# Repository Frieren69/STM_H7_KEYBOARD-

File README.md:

# STM_H7_KEYBOARD-
An keyboard with STM 32H7

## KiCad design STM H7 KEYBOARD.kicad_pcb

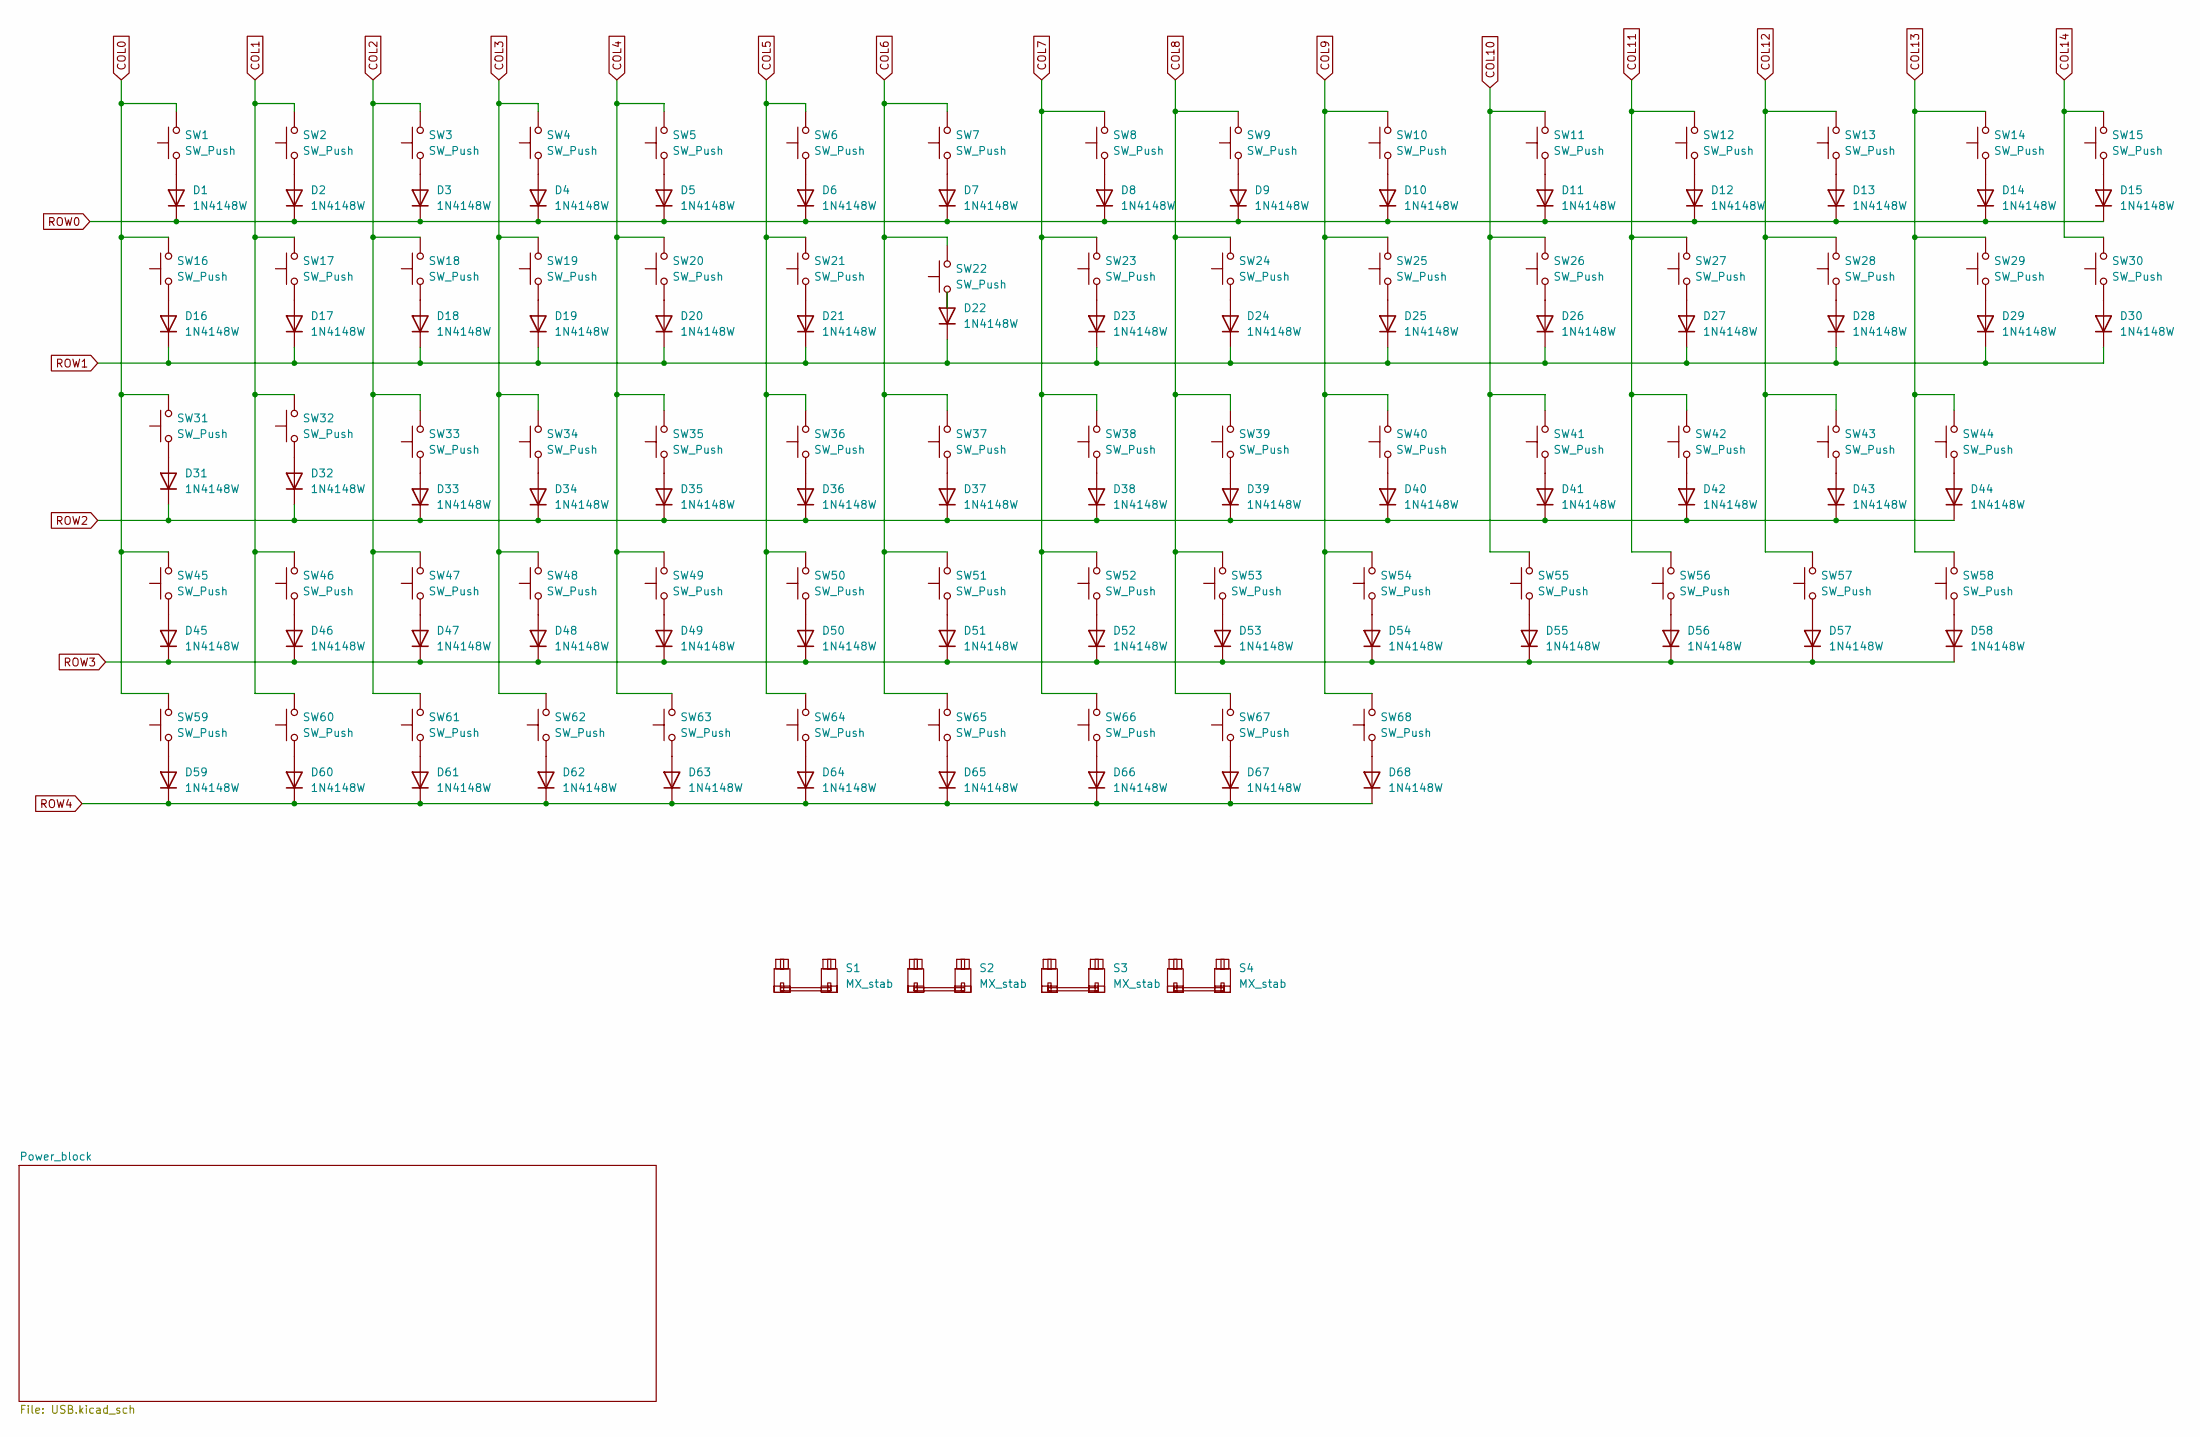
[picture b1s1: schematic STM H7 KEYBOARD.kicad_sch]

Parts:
D1, D2, D3, D4, D5, D6, D7, D8, D9, D10, D11, D12, D13, D14, D15, D16, D17, D18, D19, D20, D21, D22, D23, D24, D25, D26, D27, D28, D29, D30, D31, D32, D33, D34, D35, D36, D37, D38, D39, D40, D41, D42, D43, D44, D45, D46, D47, D48, D49, D50, D51, D52, D53, D54, D55, D56, D57, D58, D59, D60, D61, D62, D63, D64, D65, D66, D67, D68: 1N4148W; D_SOD-123
S1: MX_stab; STAB_MX_P_6.25u
S2, S3, S4: MX_stab; STAB_MX_P_2u
SW1, SW2, SW3, SW4, SW5, SW6, SW7, SW8, SW9, SW10, SW11, SW12, SW13, SW14, SW15, SW16, SW17, SW18, SW19, SW20, SW21, SW22, SW23, SW24, SW25, SW26, SW27, SW28, SW29, SW30, SW31, SW32, SW33, SW34, SW35, SW36, SW37, SW38, SW39, SW40, SW41, SW42, SW43, SW44, SW45, SW46, SW47, SW48, SW49, SW50, SW51, SW52, SW53, SW54, SW55, SW56, SW57, SW58, SW59, SW60, SW61, SW62, SW63, SW64, SW65, SW66, SW67, SW68: SW_Push; SW_MX_Hotswap_C49352235_5Pin

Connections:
COL0: SW1.2, SW16.2, SW31.2, SW45.2, SW59.2
COL1: SW2.2, SW17.2, SW32.2, SW46.2, SW60.2
COL2: SW3.2, SW18.2, SW33.2, SW47.2, SW61.2
COL3: SW4.2, SW19.2, SW34.2, SW48.2, SW62.2
COL4: SW5.2, SW20.2, SW35.2, SW49.2, SW63.2
COL5: SW6.2, SW21.2, SW36.2, SW50.2, SW64.2
COL6: SW7.2, SW22.2, SW37.2, SW51.2, SW65.2
COL7: SW8.2, SW23.2, SW38.2, SW52.2, SW66.2
COL8: SW9.2, SW24.2, SW39.2, SW53.2, SW67.2
COL9: SW10.2, SW25.2, SW40.2, SW54.2, SW68.2
COL10: SW11.2, SW26.2, SW41.2, SW55.2
COL11: SW12.2, SW27.2, SW42.2, SW56.2
COL12: SW13.2, SW28.2, SW43.2, SW57.2
COL13: SW14.2, SW29.2, SW44.2, SW58.2
COL14: SW15.2, SW30.2
unnamed: D1.2 (A), SW1.1
unnamed: D2.2 (A), SW2.1
unnamed: D3.2 (A), SW3.1
unnamed: D4.2 (A), SW4.1
unnamed: D5.2 (A), SW5.1
unnamed: D6.2 (A), SW6.1
unnamed: D7.2 (A), SW7.1
unnamed: D8.2 (A), SW8.1
unnamed: D9.2 (A), SW9.1
unnamed: D10.2 (A), SW10.1
unnamed: D11.2 (A), SW11.1
unnamed: D12.2 (A), SW12.1
unnamed: D13.2 (A), SW13.1
unnamed: D14.2 (A), SW14.1
unnamed: D15.2 (A), SW15.1
unnamed: D16.2 (A), SW16.1
unnamed: D17.2 (A), SW17.1
unnamed: D18.2 (A), SW18.1
unnamed: D19.2 (A), SW19.1
unnamed: D20.2 (A), SW20.1
unnamed: D21.2 (A), SW21.1
unnamed: D22.2 (A), SW22.1
unnamed: D23.2 (A), SW23.1
unnamed: D24.2 (A), SW24.1
unnamed: D25.2 (A), SW25.1
unnamed: D26.2 (A), SW26.1
unnamed: D27.2 (A), SW27.1
unnamed: D28.2 (A), SW28.1
unnamed: D29.2 (A), SW29.1
unnamed: D30.2 (A), SW30.1
unnamed: D31.2 (A), SW31.1
unnamed: D32.2 (A), SW32.1
unnamed: D33.2 (A), SW33.1
unnamed: D34.2 (A), SW34.1
unnamed: D35.2 (A), SW35.1
unnamed: D36.2 (A), SW36.1
unnamed: D37.2 (A), SW37.1
unnamed: D38.2 (A), SW38.1
unnamed: D39.2 (A), SW39.1
unnamed: D40.2 (A), SW40.1
unnamed: D41.2 (A), SW41.1
unnamed: D42.2 (A), SW42.1
unnamed: D43.2 (A), SW43.1
unnamed: D44.2 (A), SW44.1
unnamed: D45.2 (A), SW45.1
unnamed: D46.2 (A), SW46.1
unnamed: D47.2 (A), SW47.1
unnamed: D48.2 (A), SW48.1
unnamed: D49.2 (A), SW49.1
unnamed: D50.2 (A), SW50.1
unnamed: D51.2 (A), SW51.1
unnamed: D52.2 (A), SW52.1
unnamed: D53.2 (A), SW53.1
unnamed: D54.2 (A), SW54.1
unnamed: D55.2 (A), SW55.1
unnamed: D56.2 (A), SW56.1
unnamed: D57.2 (A), SW57.1
unnamed: D58.2 (A), SW58.1
unnamed: D59.2 (A), SW59.1
unnamed: D60.2 (A), SW60.1
unnamed: D61.2 (A), SW61.1
unnamed: D62.2 (A), SW62.1
unnamed: D63.2 (A), SW63.1
unnamed: D64.2 (A), SW64.1
unnamed: D65.2 (A), SW65.1
unnamed: D66.2 (A), SW66.1
unnamed: D67.2 (A), SW67.1
unnamed: D68.2 (A), SW68.1
ROW0: D1.1 (K), D2.1 (K), D3.1 (K), D4.1 (K), D5.1 (K), D6.1 (K), D7.1 (K), D8.1 (K), D9.1 (K), D10.1 (K), D11.1 (K), D12.1 (K), D13.1 (K), D14.1 (K), D15.1 (K)
ROW1: D16.1 (K), D17.1 (K), D18.1 (K), D19.1 (K), D20.1 (K), D21.1 (K), D22.1 (K), D23.1 (K), D24.1 (K), D25.1 (K), D26.1 (K), D27.1 (K), D28.1 (K), D29.1 (K), D30.1 (K)
ROW2: D31.1 (K), D32.1 (K), D33.1 (K), D34.1 (K), D35.1 (K), D36.1 (K), D37.1 (K), D38.1 (K), D39.1 (K), D40.1 (K), D41.1 (K), D42.1 (K), D43.1 (K), D44.1 (K)
ROW3: D45.1 (K), D46.1 (K), D47.1 (K), D48.1 (K), D49.1 (K), D50.1 (K), D51.1 (K), D52.1 (K), D53.1 (K), D54.1 (K), D55.1 (K), D56.1 (K), D57.1 (K), D58.1 (K)
ROW4: D59.1 (K), D60.1 (K), D61.1 (K), D62.1 (K), D63.1 (K), D64.1 (K), D65.1 (K), D66.1 (K), D67.1 (K), D68.1 (K)

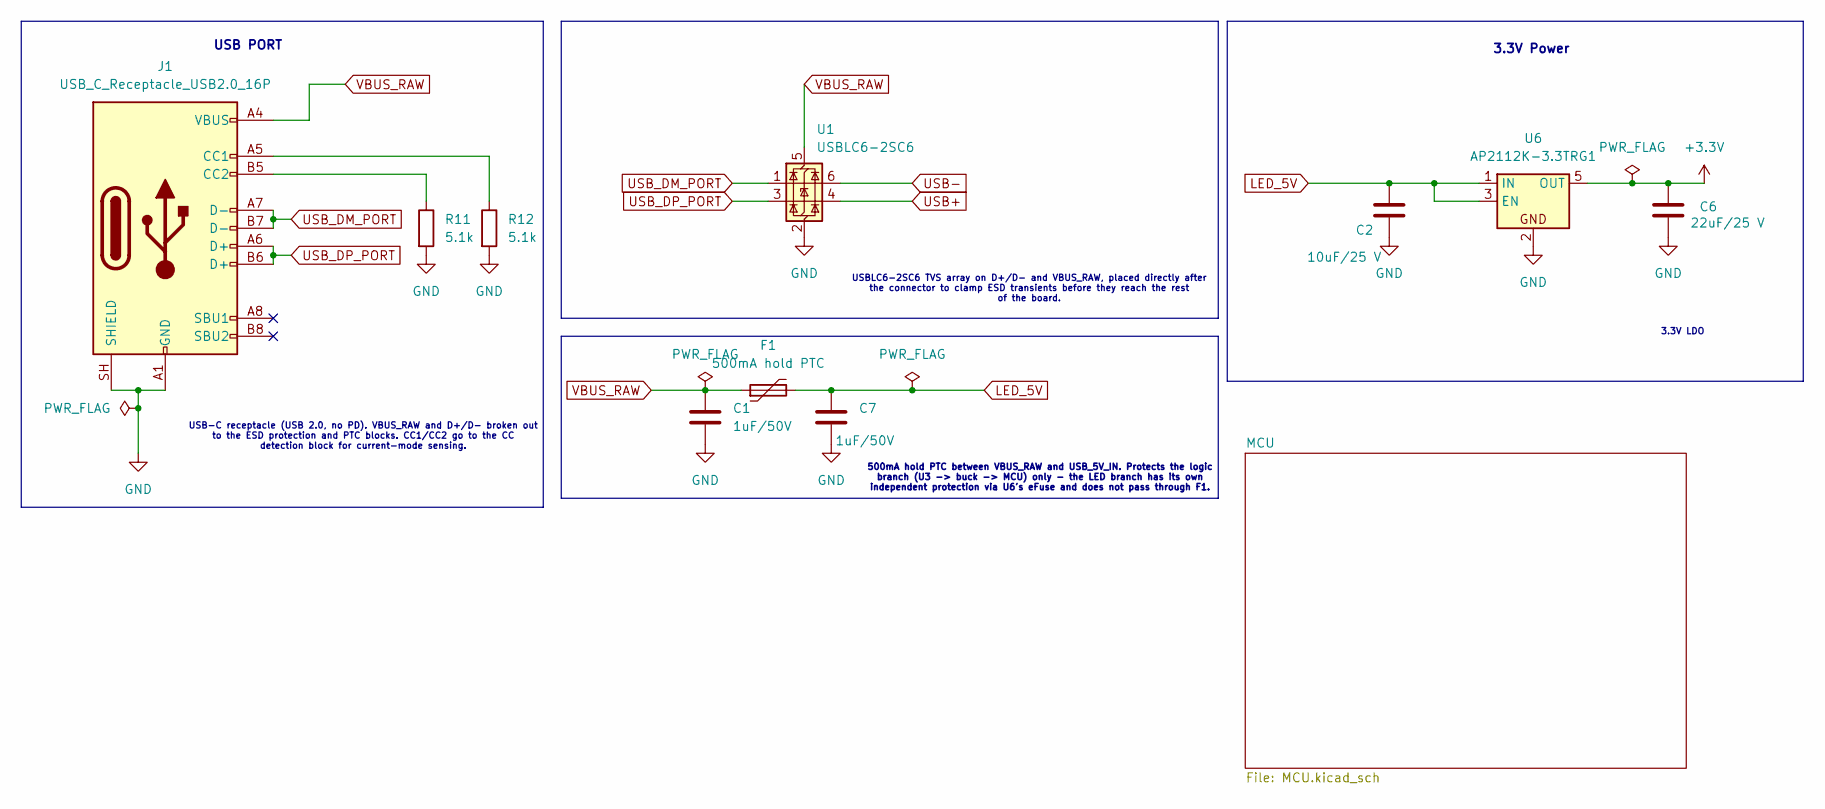
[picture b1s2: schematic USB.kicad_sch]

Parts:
C1, C7: 1uF/50V; C_0805_2012Metric
C2: 10uF/25 V; C_0805_2012Metric
C6: 22uF/25 V; C_0805_2012Metric
F1: 500mA hold PTC; Fuse_1206_3216Metric
J1: USB_C_Receptacle_USB2.0_16P; USB_C_Receptacle_HRO_TYPE-C-31-M-12
R11, R12: 5.1k; R_0603_1608Metric
U1: USBLC6-2SC6; SOT-23-6
U6: AP2112K-3.3TRG1; SOT-23-5

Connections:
+3.3V: C6.1, U6.5 (OUT); also elsewhere on the board
GND: C1.2, C2.2, C6.2, C7.2, J1.A1 (GND), J1.A12 (GND), J1.B1 (GND), J1.B12 (GND), J1.SH (SHIELD), R11.2, R12.2, U1.2 (GND), U6.2; also elsewhere on the board
LED_5V: C2.1, C7.1, F1.2, U6.1 (IN), U6.3 (EN); also elsewhere on the board
unnamed: J1.A5 (CC1), R12.1
unnamed: J1.B5 (CC2), R11.1
USB+: U1.4 (I/O2); also elsewhere on the board
USB-: U1.6 (I/O1); also elsewhere on the board
USB_DM_PORT: J1.A7 (D-), J1.B7 (D-), U1.1 (I/O1)
USB_DP_PORT: J1.A6 (D+), J1.B6 (D+), U1.3 (I/O2)
VBUS_RAW: C1.1, F1.1, J1.A4 (VBUS), J1.A9 (VBUS), J1.B4 (VBUS), J1.B9 (VBUS), U1.5 (VBUS)

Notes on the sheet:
USBLC6-2SC6 TVS array on D+/D- and VBUS_RAW, placed directly after the connector to clamp ESD transients before they reach the rest of the board.
USB-C receptacle (USB 2.0, no PD). VBUS_RAW and D+/D- broken out to the ESD protection and PTC blocks. CC1/CC2 go to the CC detection block for current-mode sensing.
USB PORT
3.3V Power
500mA hold PTC between VBUS_RAW and USB_5V_IN. Protects the logic branch (U3 -> buck -> MCU) only - the LED branch has its own independent protection via U6's eFuse and does not pass through F1.
3.3V LDO

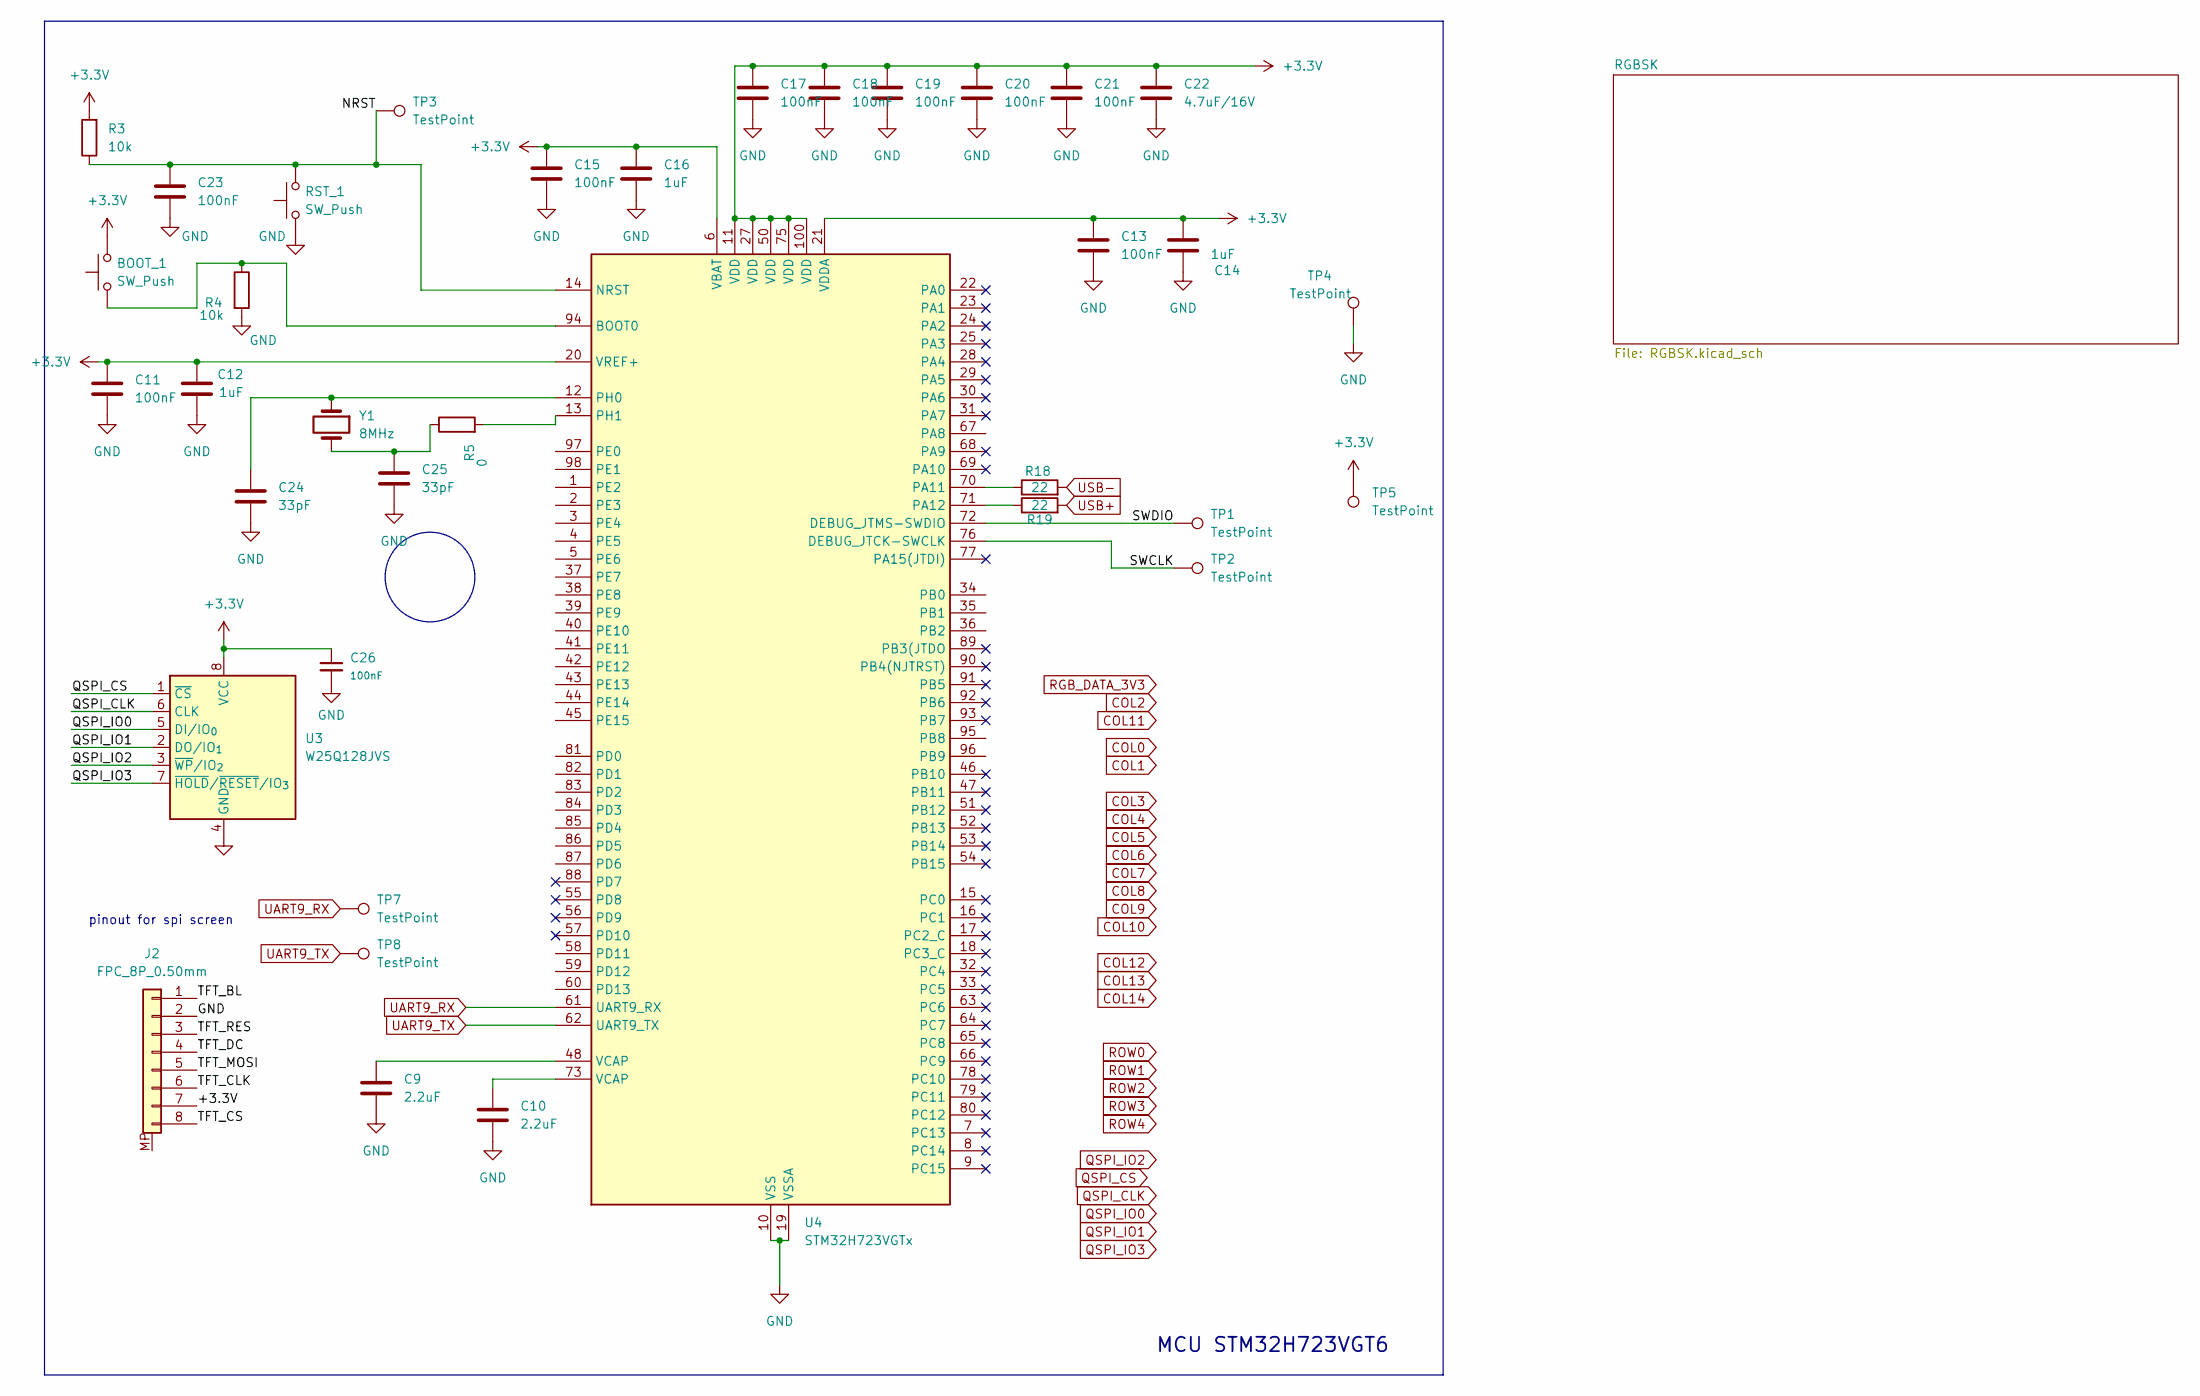
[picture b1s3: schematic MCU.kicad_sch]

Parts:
BOOT_1: SW_Push; SW_SPST_TL3342
C9, C10: 2.2uF; C_0603_1608Metric
C11, C13, C15, C17, C18, C19, C20, C21, C23: 100nF; C_0603_1608Metric
C12, C14, C16: 1uF; C_0805_2012Metric
C22: 4.7uF/16V; C_0603_1608Metric
C24, C25: 33pF; C_0603_1608Metric
C26: 100nF; C_0402
J2: FPC_8P_0.50mm; XUNPU_FPC-05F-8PH20_1x8-1MP_P0.5mm
R3, R4: 10k; R_0603_1608Metric
R5: 0; R_0603_1608Metric
R18, R19: 22; R_0603_1608Metric
RST_1: SW_Push; SW_SPST_TL3342
TP1, TP2, TP3, TP4, TP5, TP7, TP8: TestPoint; TestPoint_Pad_D2.0mm
U3: W25Q128JVS; SOIC-8_5.3x5.3mm_P1.27mm; LCSC C97521
U4: STM32H723VGTx; LQFP-100_14x14mm_P0.5mm; LCSC C730142
Y1: 8MHz; Crystal_SMD_5032-2Pin_5.0x3.2mm; LCSC C115962

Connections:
+3.3V: BOOT_1.2, C11.1, C12.1, C13.1, C14.1, C15.1, C16.1, C17.1, C18.1, C19.1, C20.1, C21.1, C22.1, C26.1, R3.2, TP5.1 (1_1), U3.8 (VCC), U4.6 (VBAT), U4.11 (VDD), U4.20 (VREF+), U4.21 (VDDA), U4.27 (VDD), U4.50 (VDD), U4.75 (VDD), U4.100 (VDD); also elsewhere on the board
/Power_block/MCU/NRST: C23.1, R3.1, RST_1.2, TP3.1 (1_1), U4.14 (NRST)
/Power_block/MCU/SWCLK: TP2.1 (1_1), U4.76 (DEBUG_JTCK-SWCLK)
/Power_block/MCU/SWDIO: TP1.1 (1_1), U4.72 (DEBUG_JTMS-SWDIO)
GND: C9.2, C10.2, C11.2, C12.2, C13.2, C14.2, C15.2, C16.2, C17.2, C18.2, C19.2, C20.2, C21.2, C22.2, C23.2, C24.2, C25.2, C26.2, R4.2, RST_1.1, TP4.1 (1_1), U3.4 (GND), U4.10 (VSS), U4.19 (VSSA), U4.26 (VSS), U4.49 (VSS), U4.74 (VSS), U4.99 (VSS); also elsewhere on the board
unnamed: C9.1, U4.48 (VCAP)
unnamed: C10.1, U4.73 (VCAP)
unnamed: C25.1, R5.1, Y1.2
unnamed: BOOT_1.1, R4.1, U4.94 (BOOT0)
unnamed: R18.1, U4.70 (PA11)
unnamed: R19.1, U4.71 (PA12)
unnamed: C24.1, U4.12 (PH0), Y1.1
unnamed: R5.2, U4.13 (PH1)
QSPI_CLK: U3.6 (CLK)
QSPI_CS: U3.1 (~CS)
QSPI_IO0: U3.5 (DI/IO_{0})
QSPI_IO1: U3.2 (DO/IO_{1})
QSPI_IO2: U3.3 (~WP/IO_{2})
QSPI_IO3: U3.7 (~HOLD/~RESET/IO_{3})
UART9_RX: TP7.1 (1_1), U4.61 (UART9_RX)
UART9_TX: TP8.1 (1_1), U4.62 (UART9_TX)
USB+: R19.2; also elsewhere on the board
USB-: R18.2; also elsewhere on the board

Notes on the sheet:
pinout for spi screen
MCU STM32H723VGT6

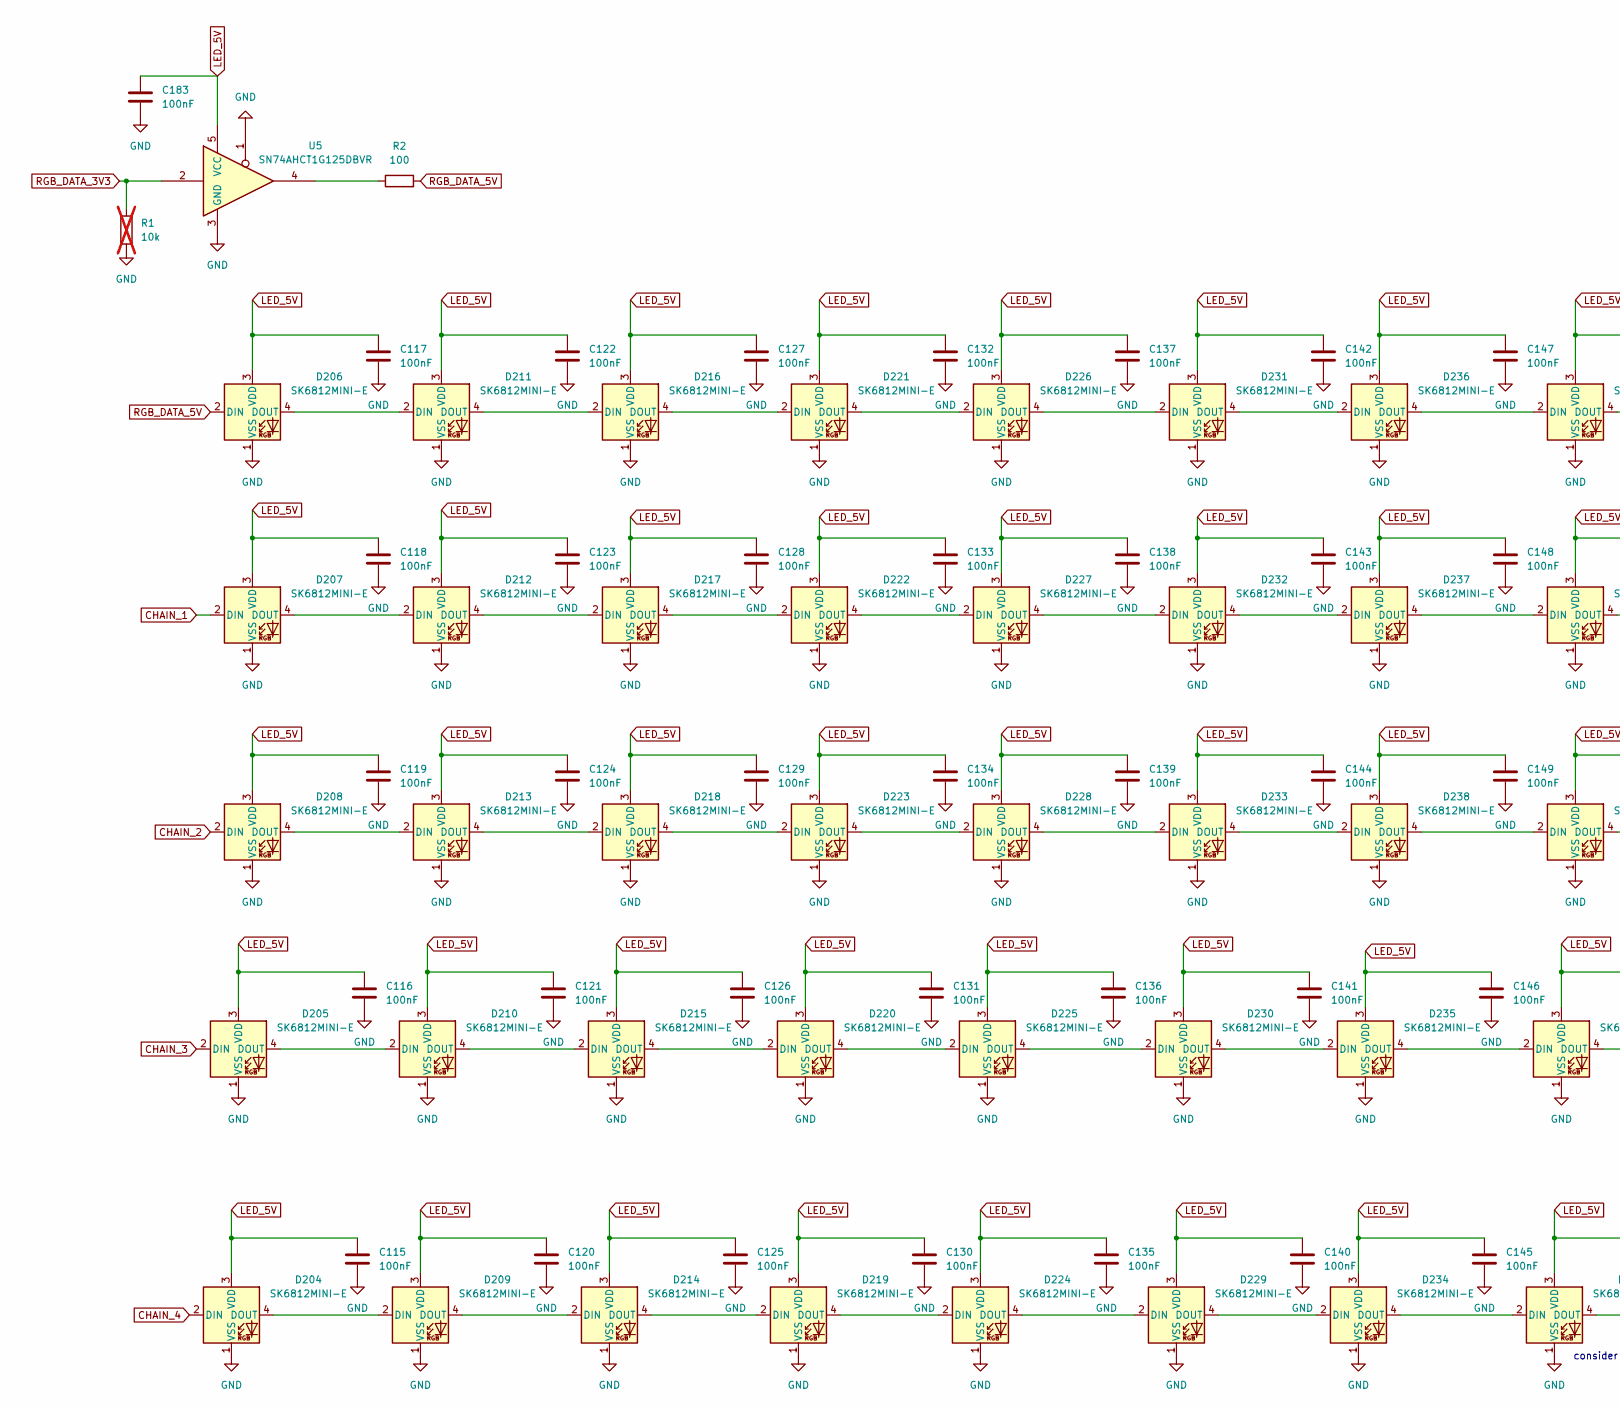
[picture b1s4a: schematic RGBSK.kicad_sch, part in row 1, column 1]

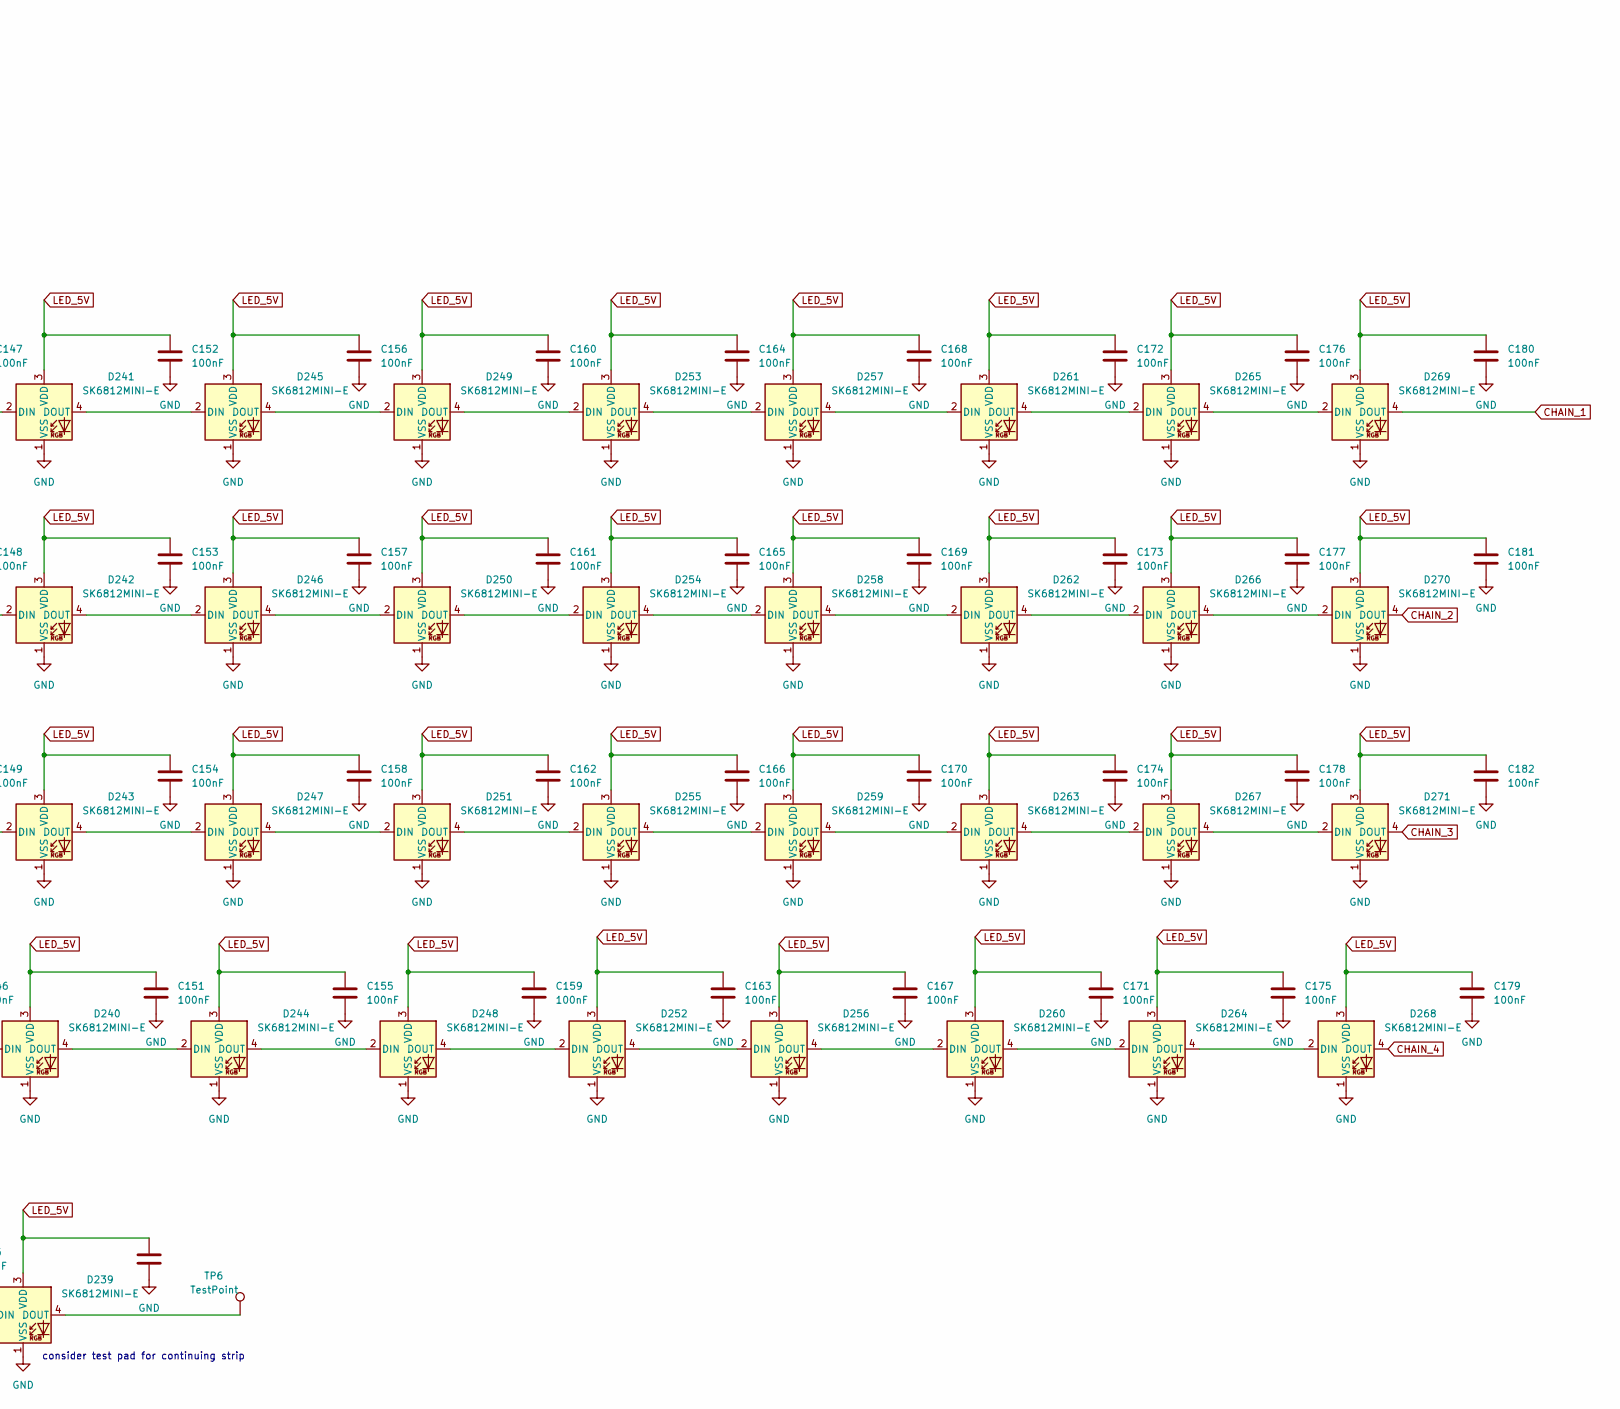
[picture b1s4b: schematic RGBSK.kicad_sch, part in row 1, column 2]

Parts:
C115, C116, C117, C118, C119, C120, C121, C122, C123, C124, C125, C126, C127, C128, C129, C130, C131, C132, C133, C134, C135, C136, C137, C138, C139, C140, C141, C142, C143, C144, C145, C146, C147, C148, C149, C150, C151, C152, C153, C154, C155, C156, C157, C158, C159, C160, C161, C162, C163, C164, C165, C166, C167, C168, C169, C170, C171, C172, C173, C174, C175, C176, C177, C178, C179, C180, C181, C182, C183: 100nF; C_0402_1005Metric
D204, D205, D206, D207, D208, D209, D210, D211, D212, D213, D214, D215, D216, D217, D218, D219, D220, D221, D222, D223, D224, D225, D226, D227, D228, D229, D230, D231, D232, D233, D234, D235, D236, D237, D238, D239, D240, D241, D242, D243, D244, D245, D246, D247, D248, D249, D250, D251, D252, D253, D254, D255, D256, D257, D258, D259, D260, D261, D262, D263, D264, D265, D266, D267, D268, D269, D270, D271: SK6812MINI-E; LED_SK6812MINI-E_3.2x2.8mm_P1.5mm_ReverseMount
R1: 10k; R_0402_1005Metric; not fitted
R2: 100; R_0402_1005Metric
TP6: TestPoint; TestPoint_Pad_D2.0mm
U5: SN74AHCT1G125DBVR; SOT-23-5

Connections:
CHAIN_1: D207.2 (DIN), D269.4 (DOUT)
CHAIN_2: D208.2 (DIN), D270.4 (DOUT)
CHAIN_3: D205.2 (DIN), D271.4 (DOUT)
CHAIN_4: D204.2 (DIN), D268.4 (DOUT)
GND: C115.2, C116.2, C117.2, C118.2, C119.2, C120.2, C121.2, C122.2, C123.2, C124.2, C125.2, C126.2, C127.2, C128.2, C129.2, C130.2, C131.2, C132.2, C133.2, C134.2, C135.2, C136.2, C137.2, C138.2, C139.2, C140.2, C141.2, C142.2, C143.2, C144.2, C145.2, C146.2, C147.2, C148.2, C149.2, C150.2, C151.2, C152.2, C153.2, C154.2, C155.2, C156.2, C157.2, C158.2, C159.2, C160.2, C161.2, C162.2, C163.2, C164.2, C165.2, C166.2, C167.2, C168.2, C169.2, C170.2, C171.2, C172.2, C173.2, C174.2, C175.2, C176.2, C177.2, C178.2, C179.2, C180.2, C181.2, C182.2, C183.2, D204.1 (VSS), D205.1 (VSS), D206.1 (VSS), D207.1 (VSS), D208.1 (VSS), D209.1 (VSS), D210.1 (VSS), D211.1 (VSS), D212.1 (VSS), D213.1 (VSS), D214.1 (VSS), D215.1 (VSS), D216.1 (VSS), D217.1 (VSS), D218.1 (VSS), D219.1 (VSS), D220.1 (VSS), D221.1 (VSS), D222.1 (VSS), D223.1 (VSS), D224.1 (VSS), D225.1 (VSS), D226.1 (VSS), D227.1 (VSS), D228.1 (VSS), D229.1 (VSS), D230.1 (VSS), D231.1 (VSS), D232.1 (VSS), D233.1 (VSS), D234.1 (VSS), D235.1 (VSS), D236.1 (VSS), D237.1 (VSS), D238.1 (VSS), D239.1 (VSS), D240.1 (VSS), D241.1 (VSS), D242.1 (VSS), D243.1 (VSS), D244.1 (VSS), D245.1 (VSS), D246.1 (VSS), D247.1 (VSS), D248.1 (VSS), D249.1 (VSS), D250.1 (VSS), D251.1 (VSS), D252.1 (VSS), D253.1 (VSS), D254.1 (VSS), D255.1 (VSS), D256.1 (VSS), D257.1 (VSS), D258.1 (VSS), D259.1 (VSS), D260.1 (VSS), D261.1 (VSS), D262.1 (VSS), D263.1 (VSS), D264.1 (VSS), D265.1 (VSS), D266.1 (VSS), D267.1 (VSS), D268.1 (VSS), D269.1 (VSS), D270.1 (VSS), D271.1 (VSS), R1.2, U5.1, U5.3 (GND); also elsewhere on the board
LED_5V: C115.1, C116.1, C117.1, C118.1, C119.1, C120.1, C121.1, C122.1, C123.1, C124.1, C125.1, C126.1, C127.1, C128.1, C129.1, C130.1, C131.1, C132.1, C133.1, C134.1, C135.1, C136.1, C137.1, C138.1, C139.1, C140.1, C141.1, C142.1, C143.1, C144.1, C145.1, C146.1, C147.1, C148.1, C149.1, C150.1, C151.1, C152.1, C153.1, C154.1, C155.1, C156.1, C157.1, C158.1, C159.1, C160.1, C161.1, C162.1, C163.1, C164.1, C165.1, C166.1, C167.1, C168.1, C169.1, C170.1, C171.1, C172.1, C173.1, C174.1, C175.1, C176.1, C177.1, C178.1, C179.1, C180.1, C181.1, C182.1, C183.1, D204.3 (VDD), D205.3 (VDD), D206.3 (VDD), D207.3 (VDD), D208.3 (VDD), D209.3 (VDD), D210.3 (VDD), D211.3 (VDD), D212.3 (VDD), D213.3 (VDD), D214.3 (VDD), D215.3 (VDD), D216.3 (VDD), D217.3 (VDD), D218.3 (VDD), D219.3 (VDD), D220.3 (VDD), D221.3 (VDD), D222.3 (VDD), D223.3 (VDD), D224.3 (VDD), D225.3 (VDD), D226.3 (VDD), D227.3 (VDD), D228.3 (VDD), D229.3 (VDD), D230.3 (VDD), D231.3 (VDD), D232.3 (VDD), D233.3 (VDD), D234.3 (VDD), D235.3 (VDD), D236.3 (VDD), D237.3 (VDD), D238.3 (VDD), D239.3 (VDD), D240.3 (VDD), D241.3 (VDD), D242.3 (VDD), D243.3 (VDD), D244.3 (VDD), D245.3 (VDD), D246.3 (VDD), D247.3 (VDD), D248.3 (VDD), D249.3 (VDD), D250.3 (VDD), D251.3 (VDD), D252.3 (VDD), D253.3 (VDD), D254.3 (VDD), D255.3 (VDD), D256.3 (VDD), D257.3 (VDD), D258.3 (VDD), D259.3 (VDD), D260.3 (VDD), D261.3 (VDD), D262.3 (VDD), D263.3 (VDD), D264.3 (VDD), D265.3 (VDD), D266.3 (VDD), D267.3 (VDD), D268.3 (VDD), D269.3 (VDD), D270.3 (VDD), D271.3 (VDD), U5.5 (VCC); also elsewhere on the board
unnamed: D204.4 (DOUT), D209.2 (DIN)
unnamed: D205.4 (DOUT), D210.2 (DIN)
unnamed: D206.4 (DOUT), D211.2 (DIN)
unnamed: D207.4 (DOUT), D212.2 (DIN)
unnamed: D208.4 (DOUT), D213.2 (DIN)
unnamed: D209.4 (DOUT), D214.2 (DIN)
unnamed: D210.4 (DOUT), D215.2 (DIN)
unnamed: D211.4 (DOUT), D216.2 (DIN)
unnamed: D212.4 (DOUT), D217.2 (DIN)
unnamed: D213.4 (DOUT), D218.2 (DIN)
unnamed: D214.4 (DOUT), D219.2 (DIN)
unnamed: D215.4 (DOUT), D220.2 (DIN)
unnamed: D216.4 (DOUT), D221.2 (DIN)
unnamed: D217.4 (DOUT), D222.2 (DIN)
unnamed: D218.4 (DOUT), D223.2 (DIN)
unnamed: D219.4 (DOUT), D224.2 (DIN)
unnamed: D220.4 (DOUT), D225.2 (DIN)
unnamed: D221.4 (DOUT), D226.2 (DIN)
unnamed: D222.4 (DOUT), D227.2 (DIN)
unnamed: D223.4 (DOUT), D228.2 (DIN)
unnamed: D224.4 (DOUT), D229.2 (DIN)
unnamed: D225.4 (DOUT), D230.2 (DIN)
unnamed: D226.4 (DOUT), D231.2 (DIN)
unnamed: D227.4 (DOUT), D232.2 (DIN)
unnamed: D228.4 (DOUT), D233.2 (DIN)
unnamed: D229.4 (DOUT), D234.2 (DIN)
unnamed: D230.4 (DOUT), D235.2 (DIN)
unnamed: D231.4 (DOUT), D236.2 (DIN)
unnamed: D232.4 (DOUT), D237.2 (DIN)
unnamed: D233.4 (DOUT), D238.2 (DIN)
unnamed: D234.4 (DOUT), D239.2 (DIN)
unnamed: D235.4 (DOUT), D240.2 (DIN)
unnamed: D236.4 (DOUT), D241.2 (DIN)
unnamed: D237.4 (DOUT), D242.2 (DIN)
unnamed: D238.4 (DOUT), D243.2 (DIN)
unnamed: D239.4 (DOUT), TP6.1 (1_1)
unnamed: D240.4 (DOUT), D244.2 (DIN)
unnamed: D241.4 (DOUT), D245.2 (DIN)
unnamed: D242.4 (DOUT), D246.2 (DIN)
unnamed: D243.4 (DOUT), D247.2 (DIN)
unnamed: D244.4 (DOUT), D248.2 (DIN)
unnamed: D245.4 (DOUT), D249.2 (DIN)
unnamed: D246.4 (DOUT), D250.2 (DIN)
unnamed: D247.4 (DOUT), D251.2 (DIN)
unnamed: D248.4 (DOUT), D252.2 (DIN)
unnamed: D249.4 (DOUT), D253.2 (DIN)
unnamed: D250.4 (DOUT), D254.2 (DIN)
unnamed: D251.4 (DOUT), D255.2 (DIN)
unnamed: D252.4 (DOUT), D256.2 (DIN)
unnamed: D253.4 (DOUT), D257.2 (DIN)
unnamed: D254.4 (DOUT), D258.2 (DIN)
unnamed: D255.4 (DOUT), D259.2 (DIN)
unnamed: D256.4 (DOUT), D260.2 (DIN)
unnamed: D257.4 (DOUT), D261.2 (DIN)
unnamed: D258.4 (DOUT), D262.2 (DIN)
unnamed: D259.4 (DOUT), D263.2 (DIN)
unnamed: D260.4 (DOUT), D264.2 (DIN)
unnamed: D261.4 (DOUT), D265.2 (DIN)
unnamed: D262.4 (DOUT), D266.2 (DIN)
unnamed: D263.4 (DOUT), D267.2 (DIN)
unnamed: D264.4 (DOUT), D268.2 (DIN)
unnamed: D265.4 (DOUT), D269.2 (DIN)
unnamed: D266.4 (DOUT), D270.2 (DIN)
unnamed: D267.4 (DOUT), D271.2 (DIN)
unnamed: R2.1, U5.4
RGB_DATA_3V3: R1.1, U5.2; also elsewhere on the board
RGB_DATA_5V: D206.2 (DIN), R2.2

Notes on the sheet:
consider test pad for continuing strip

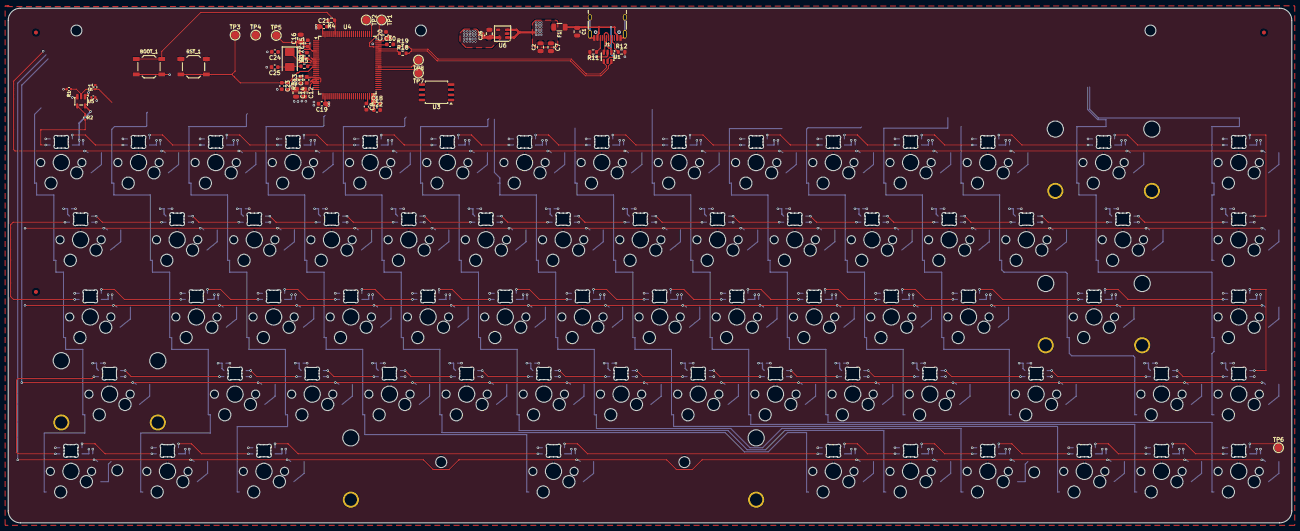
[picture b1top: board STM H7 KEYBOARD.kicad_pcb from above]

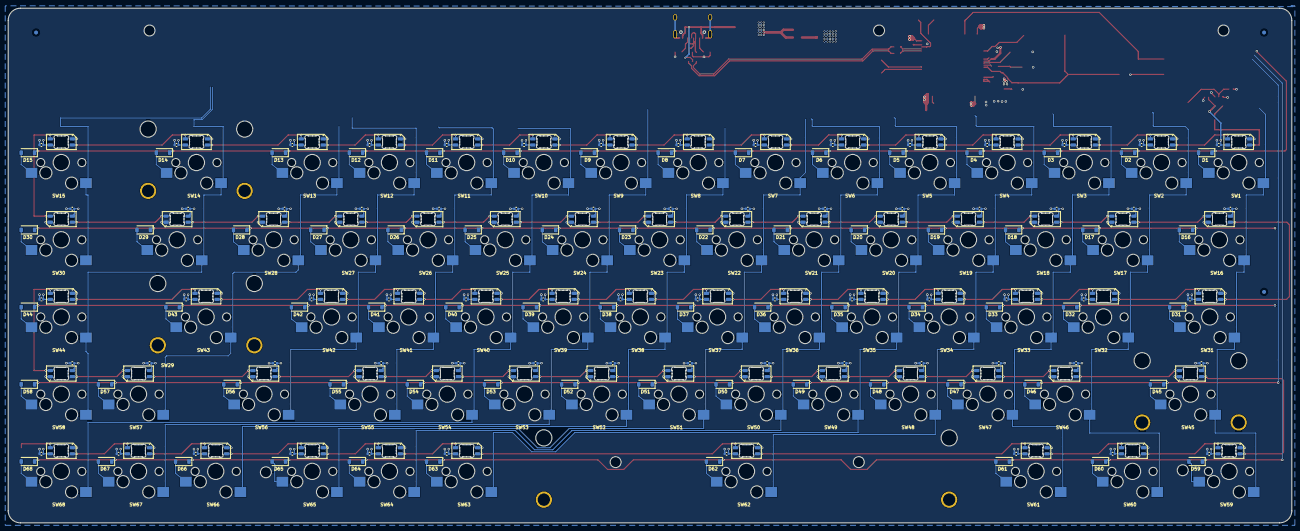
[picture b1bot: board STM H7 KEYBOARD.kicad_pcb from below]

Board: 4 copper layers, 316.7 x 127.0 mm, 340 parts (275 on the bottom side), 182 nets.

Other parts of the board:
FID1, FID2, FID3, FID4, FID5, FID6: Fiducial_1mm_Mask2mm
H1, H2, H4, H5, H6, H7, H8: MountingHole; MountingHole_2.7mm_M2.5
R1#2: 10k; R_0402_1005Metric

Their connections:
GND: R1#2.2; also elsewhere on the board
RGB_DATA_3V3: R1#2.1; also elsewhere on the board
